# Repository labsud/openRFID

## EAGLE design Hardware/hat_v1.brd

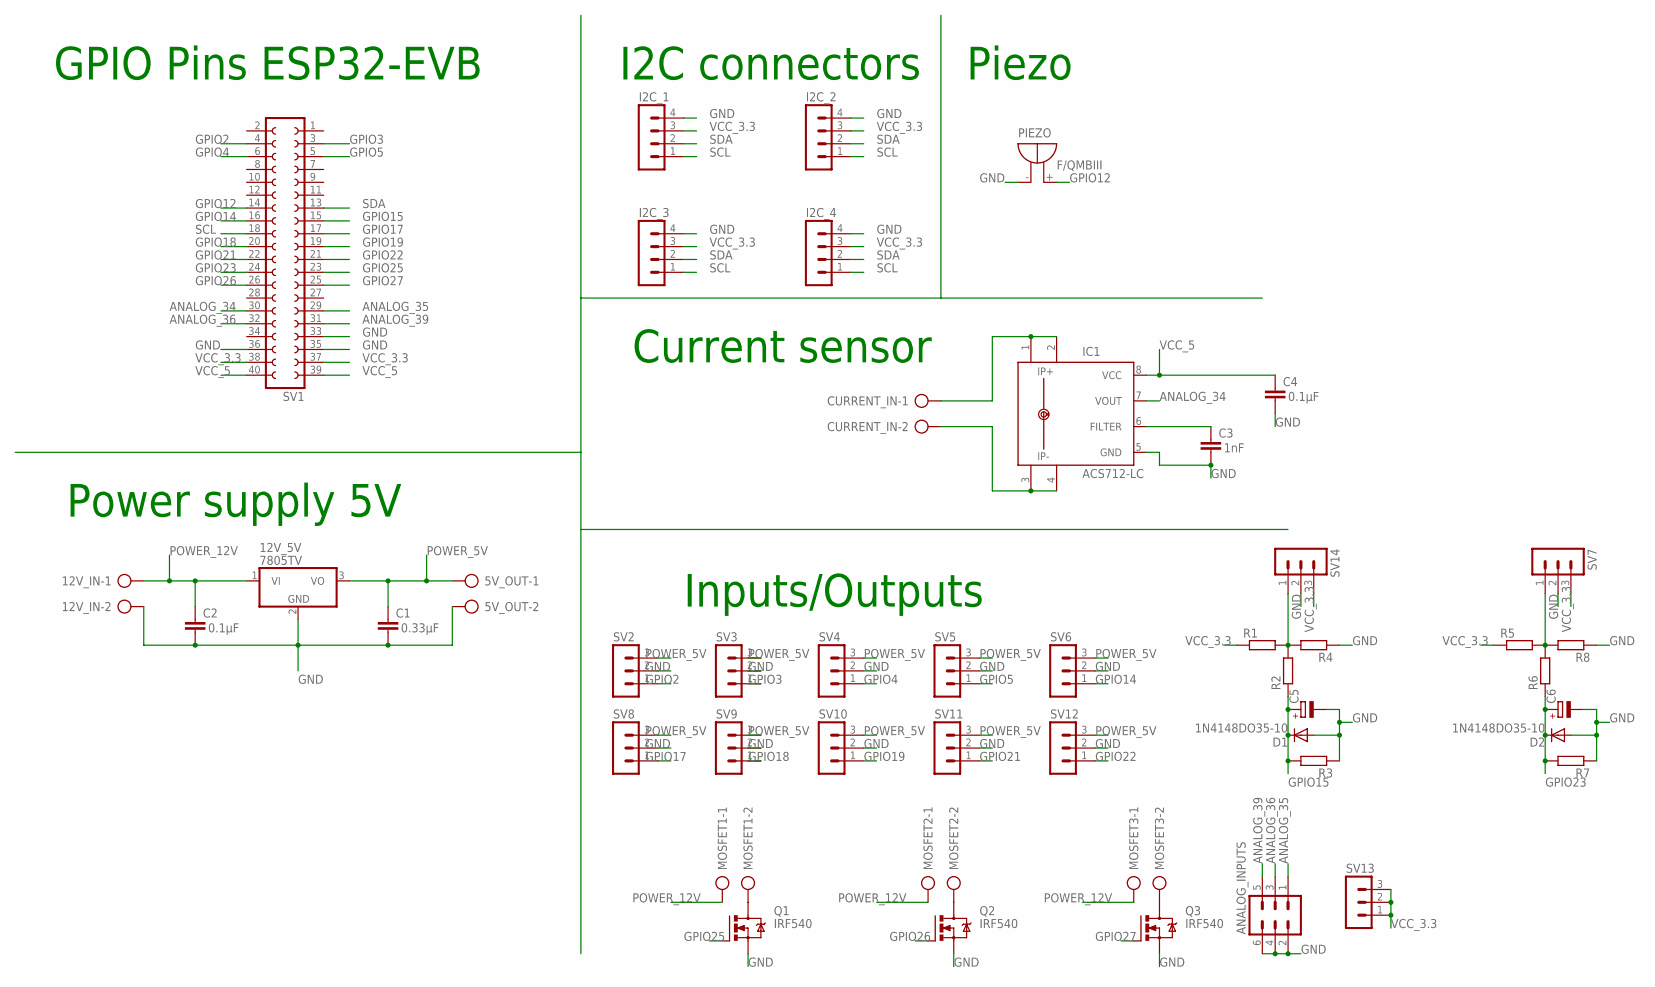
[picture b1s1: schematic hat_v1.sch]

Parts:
5V_OUT, 12V_IN: AK500/2
12V_5V: 7805TV; TO220V
ANALOG_INPUTS: MA03-2
C1: C-EU050-050X075; C050-050X075
C2: C-EU050-035X075; C050-035X075
C3, C4: C-EU025-025X050; C025-025X050
C5, C6: CPOL-EUE2.5-6; E2,5-6
CURRENT_IN: AK500/2
D1, D2: 1N4148DO35-10; DO35-10
I2C_1, I2C_2, I2C_3, I2C_4: MA04-1
IC1: ACS712-LC; SOIC8
MOSFET1, MOSFET2, MOSFET3: AK500/2
PIEZO: F/QMBIII
Q1, Q2, Q3: IRF540; TO220BV
R1, R2, R3, R5, R6, R7: R-EU_0207/2V; 0207/2V
R4, R8: R-EU_0617/5V; 0617V
SV1: FE20-2
SV2, SV3, SV4, SV5, SV6, SV7, SV8, SV9, SV10, SV11, SV12, SV13, SV14: MA03-1

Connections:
ANALOG_34: IC1.7 (VOUT), SV1.30
ANALOG_35: ANALOG_INPUTS.1, SV1.29
ANALOG_36: ANALOG_INPUTS.3, SV1.32
ANALOG_39: ANALOG_INPUTS.5, SV1.31
GND: 5V_OUT.2, 12V_5V.2 (GND), 12V_IN.2, ANALOG_INPUTS.2, ANALOG_INPUTS.4, ANALOG_INPUTS.6, C1.2, C2.2, C3.2, C4.2, C5.-, C6.-, D1.A, D2.A, I2C_1.4, I2C_2.4, I2C_3.4, I2C_4.4, IC1.5 (GND), PIEZO.- (+), Q1.S, Q2.S, Q3.S, R3.1, R4.1, R7.1, R8.1, SV1.33, SV1.35, SV1.36, SV2.2, SV3.2, SV4.2, SV5.2, SV6.2, SV7.2, SV8.2, SV9.2, SV10.2, SV11.2, SV12.2, SV14.2
GPIO2: SV1.4, SV2.1
GPIO3: SV1.3, SV3.1
GPIO4: SV1.6, SV4.1
GPIO5: SV1.5, SV5.1
GPIO12: PIEZO.+ (-), SV1.14
GPIO14: SV1.16, SV6.1
GPIO15: C5.+, D1.C, R2.1, R3.2, SV1.15
GPIO17: SV1.17, SV8.1
GPIO18: SV1.20, SV9.1
GPIO19: SV1.19, SV10.1
GPIO21: SV1.22, SV11.1
GPIO22: SV1.21, SV12.1
GPIO23: C6.+, D2.C, R6.1, R7.2, SV1.24
GPIO25: Q1.G, SV1.23
GPIO26: Q2.G, SV1.26
GPIO27: Q3.G, SV1.25
unnamed: MOSFET1.2, Q1.D
unnamed: MOSFET2.2, Q2.D
unnamed: MOSFET3.2, Q3.D
unnamed: CURRENT_IN.1, IC1.1 (IP+), IC1.2 (IP+1)
unnamed: CURRENT_IN.2, IC1.3 (IP-), IC1.4 (IP-1)
unnamed: R1.2, R2.2, R4.2, SV14.1
unnamed: R5.2, R6.2, R8.2, SV7.1
unnamed: C3.1, IC1.6 (FILTER)
POWER_5V: 5V_OUT.1, 12V_5V.3 (VO), C1.1, SV2.3, SV3.3, SV4.3, SV5.3, SV6.3, SV8.3, SV9.3, SV10.3, SV11.3, SV12.3
POWER_12V: 12V_5V.1 (VI), 12V_IN.1, C2.1, MOSFET1.1, MOSFET2.1, MOSFET3.1
SCL: I2C_1.1, I2C_2.1, I2C_3.1, I2C_4.1, SV1.18
SDA: I2C_1.2, I2C_2.2, I2C_3.2, I2C_4.2, SV1.13
VCC_3.3: I2C_1.3, I2C_2.3, I2C_3.3, I2C_4.3, R1.1, R5.1, SV1.37, SV1.38, SV7.3, SV13.1, SV13.2, SV13.3, SV14.3
VCC_5: C4.1, IC1.8 (VCC), SV1.39, SV1.40

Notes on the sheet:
I2C connectors
Current sensor
GPIO Pins ESP32-EVB
Piezo
Power supply 5V
Inputs/Outputs

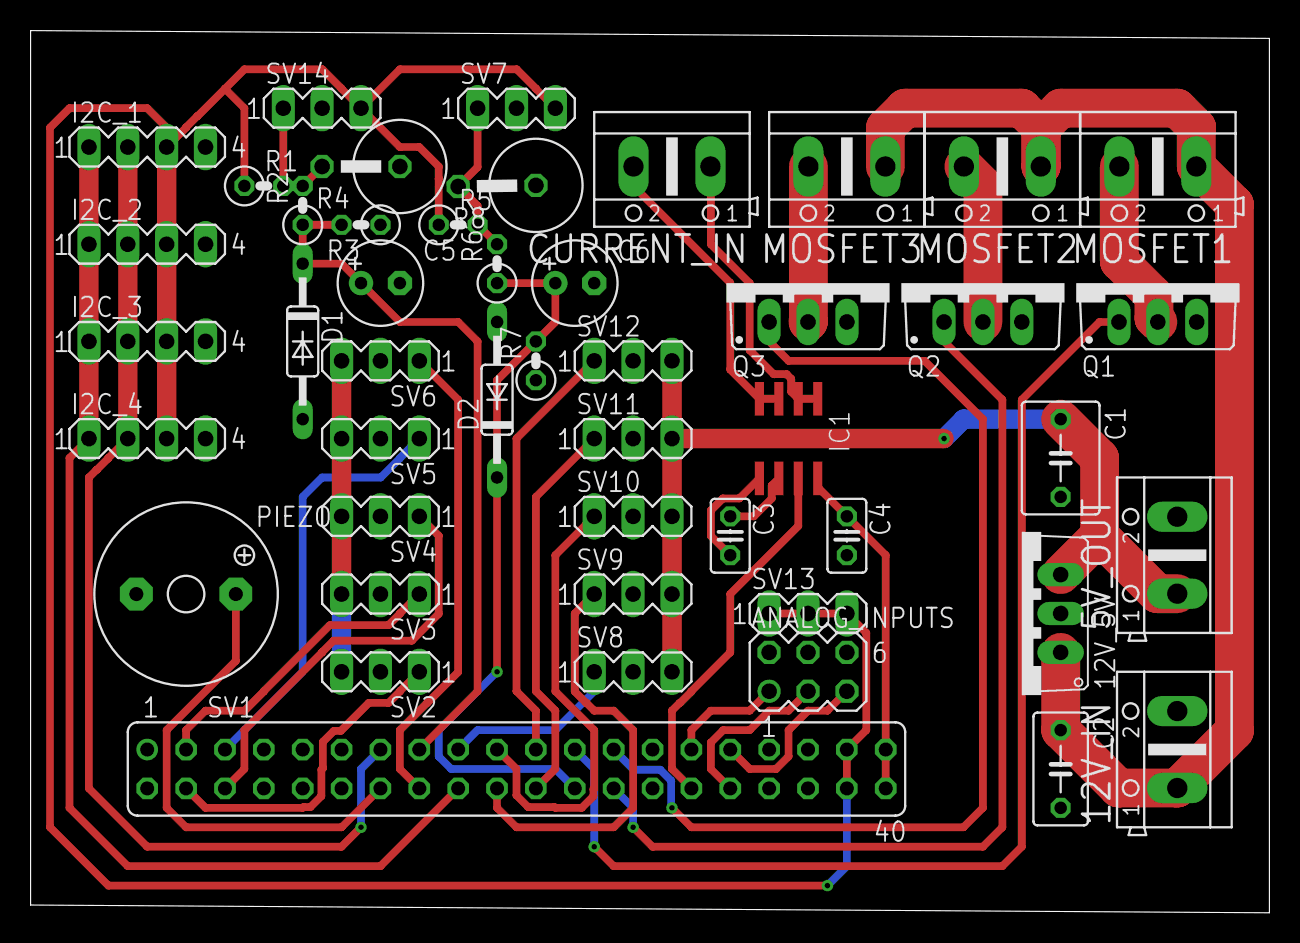
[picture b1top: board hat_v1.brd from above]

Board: 2 copper layers, 81.0 x 57.6 mm, 47 parts (0 on the bottom side), 35 nets.

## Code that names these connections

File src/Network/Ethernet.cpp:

#include "Ethernet.h"

extern "C" {
#include "WiFiGeneric.h"
};


static eth_config_t eth_config = ETH_PHY_CONF;

static void ethernet_config_gpio(void){
    // RMII data pins are fixed:
    // CRS_DRV = GPIO27
    // TXD0 = GPIO19
    // TXD1 = GPIO22
    // TX_EN = GPIO21
    // RXD0 = GPIO25
    // RXD1 = GPIO26
    // CLK == GPIO0
    phy_rmii_configure_data_interface_pins();
    // MDC is GPIO 23, MDIO is GPIO 18
    phy_rmii_smi_configure_pins(PIN_SMI_MDC, PIN_SMI_MDIO);
}

int EthernetClass::config(IPAddress local_ip, IPAddress subnet, IPAddress gateway)
{
    // stop the DHCP service
    if(tcpip_adapter_dhcpc_stop(TCPIP_ADAPTER_IF_ETH) == ESP_OK) {
        // continue
    }
    else {
        return 0;
    }

    // create a new TCP/IP info
    tcpip_adapter_ip_info_t info;
    info.ip.addr = static_cast<uint32_t>((local_ip));
    info.gw.addr = static_cast<uint32_t>((gateway));
    info.netmask.addr = static_cast<uint32_t>((subnet));
    // apply the IP settings
    if(tcpip_adapter_set_ip_info(TCPIP_ADAPTER_IF_ETH, &info) == ESP_OK) {
        // continue
    } else {
        return 0;
    }

    return 1;
}

int EthernetClass::begin()
{
    // connect the callback function
    esp_event_loop_init(&WiFiGenericClass::_eventCallback, NULL);

    // init the TCP/IP adapter
    tcpip_adapter_init();

    eth_config.phy_addr = ETH_PHY_ADDR;
    eth_config.gpio_config = ethernet_config_gpio;
    eth_config.tcpip_input = tcpip_adapter_eth_input;
    //eth_config.phy_power_enable = ethernet_power_enable;
    esp_err_t err = esp_eth_init(&eth_config);
    if(!err){
        err = esp_eth_enable();
        return 1;
    }
    return 0;
}

int EthernetClass::begin(IPAddress local_ip, IPAddress subnet, IPAddress gateway)
{
    // connect the callback function
    esp_event_loop_init(&WiFiGenericClass::_eventCallback, NULL);

    // init the TCP/IP adapter
    tcpip_adapter_init();

    // manually configure the adapter
    if(!config(local_ip,subnet,gateway))
    {
        return 0;
    }

    eth_config.phy_addr = ETH_PHY_ADDR;
    eth_config.gpio_config = ethernet_config_gpio;
    eth_config.tcpip_input = tcpip_adapter_eth_input;
    //eth_config.phy_power_enable = ethernet_power_enable;
    esp_err_t err = esp_eth_init(&eth_config);
    if(!err){
        err = esp_eth_enable();
        return 1;
    }

    return 0;
}

IPAddress EthernetClass::localIP()
{
    tcpip_adapter_ip_info_t ip;
    tcpip_adapter_get_ip_info(TCPIP_ADAPTER_IF_ETH, &ip);
    return IPAddress(ip.ip.addr);
}

IPAddress EthernetClass::subnetMask()
{
    tcpip_adapter_ip_info_t ip;
    tcpip_adapter_get_ip_info(TCPIP_ADAPTER_IF_ETH, &ip);
    return IPAddress(ip.netmask.addr);

}

IPAddress EthernetClass::gatewayIP()
{
    tcpip_adapter_ip_info_t ip;
    tcpip_adapter_get_ip_info(TCPIP_ADAPTER_IF_ETH, &ip);
    return IPAddress(ip.gw.addr);
}

bool EthernetClass::setHostname(const char * hostname)
{
    return tcpip_adapter_set_hostname(TCPIP_ADAPTER_IF_ETH, hostname) == 0;
}

bool EthernetClass::isFullDuplex()
{
    return eth_config.phy_get_duplex_mode();
}

uint8_t EthernetClass::getLinkSpeed()
{
    return eth_config.phy_get_speed_mode()?100:10;
}

String EthernetClass::getMacAddress()
{
    uint8_t mac[6];
    char macStr[18] = { 0 };
    esp_eth_get_mac(mac);
    sprintf(macStr, "%02X:%02X:%02X:%02X:%02X:%02X", mac[0], mac[1], mac[2], mac[3], mac[4], mac[5]);
    return String(macStr);
}

#if !defined(NO_GLOBAL_INSTANCES) && !defined(NO_GLOBAL_ETHERNET)
EthernetClass Ethernet;
#endif

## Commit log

2018-07-13 Dossier aRevoir supprimé
2018-07-13 Test modification archi du repo
2018-07-13 Ajout du Software
2018-07-13 Suppression des dossiers inutiles
2018-07-13 Ajout du hardware
2018-07-13 Ajout du firmware déjà compilé
2018-07-13 Ajout du fichier de config
2018-07-13 Ajout des fichiers Node-Red
2018-07-13 Ajout de la structure de la base de données
2018-07-13 Modification platformio.ini pour installation automatique des libs
